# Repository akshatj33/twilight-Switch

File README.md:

# twilight-Switch
This is the embedded C code and the schematic and board layout for my project on twilight switch.

The timely operation of street lights, porch lights and other forms of outdoor illumination is required for the twin
concerns of safety and environment protection; lights operated too late are a safety hazard, while lights operated
too early are a waste of power. The switching on and off of external lightings can be set with the help of the device
called Twilight Switch.
Traditionally switching has been controlled via a human operator or the automatic control is accomplished
using a light sensor like LDR, photosensitive cells etc. However the use of sensors is accompanied by
wastage of power deterioration over time due to incessant exposure to atmosphere and environmental
changes leading to regular maintenance.
A Twilight switch provides a mechanism by which a light bulb can be turned ON and OFF automatically
without human interference. This project is a time based solution. This mechanism works on civil twilight
time. Component used for human interface is LCD where data such as date, month, year, city and the
present time (hh:mm:ss) are entered. From the algorithm, twilight time i.e. civil-dusk and civil-dawn time of
that place is calculated.
RTC (PCF8563) is used to maintain time. As an when the civil dusk time matches with RTC, the light (here
bulb) is switched ON and remains in this state till civil-dawn time where it is toggled.
We have fabricated 2 boards. First (4*3) is the DC Circuit board which has our microcontroller
(MSP430G2553) and LCD (HD44780U). Second (3*1) is the AC circuit board which has a triac (BT136)
whose 2 of the 3 gate requires AC. We are using triac instead of a relay because SSD switches are better
than mechanical ones. To isolate the AC portion of the circuit from the DC one we have used an optoisolator
(MOC 3041).

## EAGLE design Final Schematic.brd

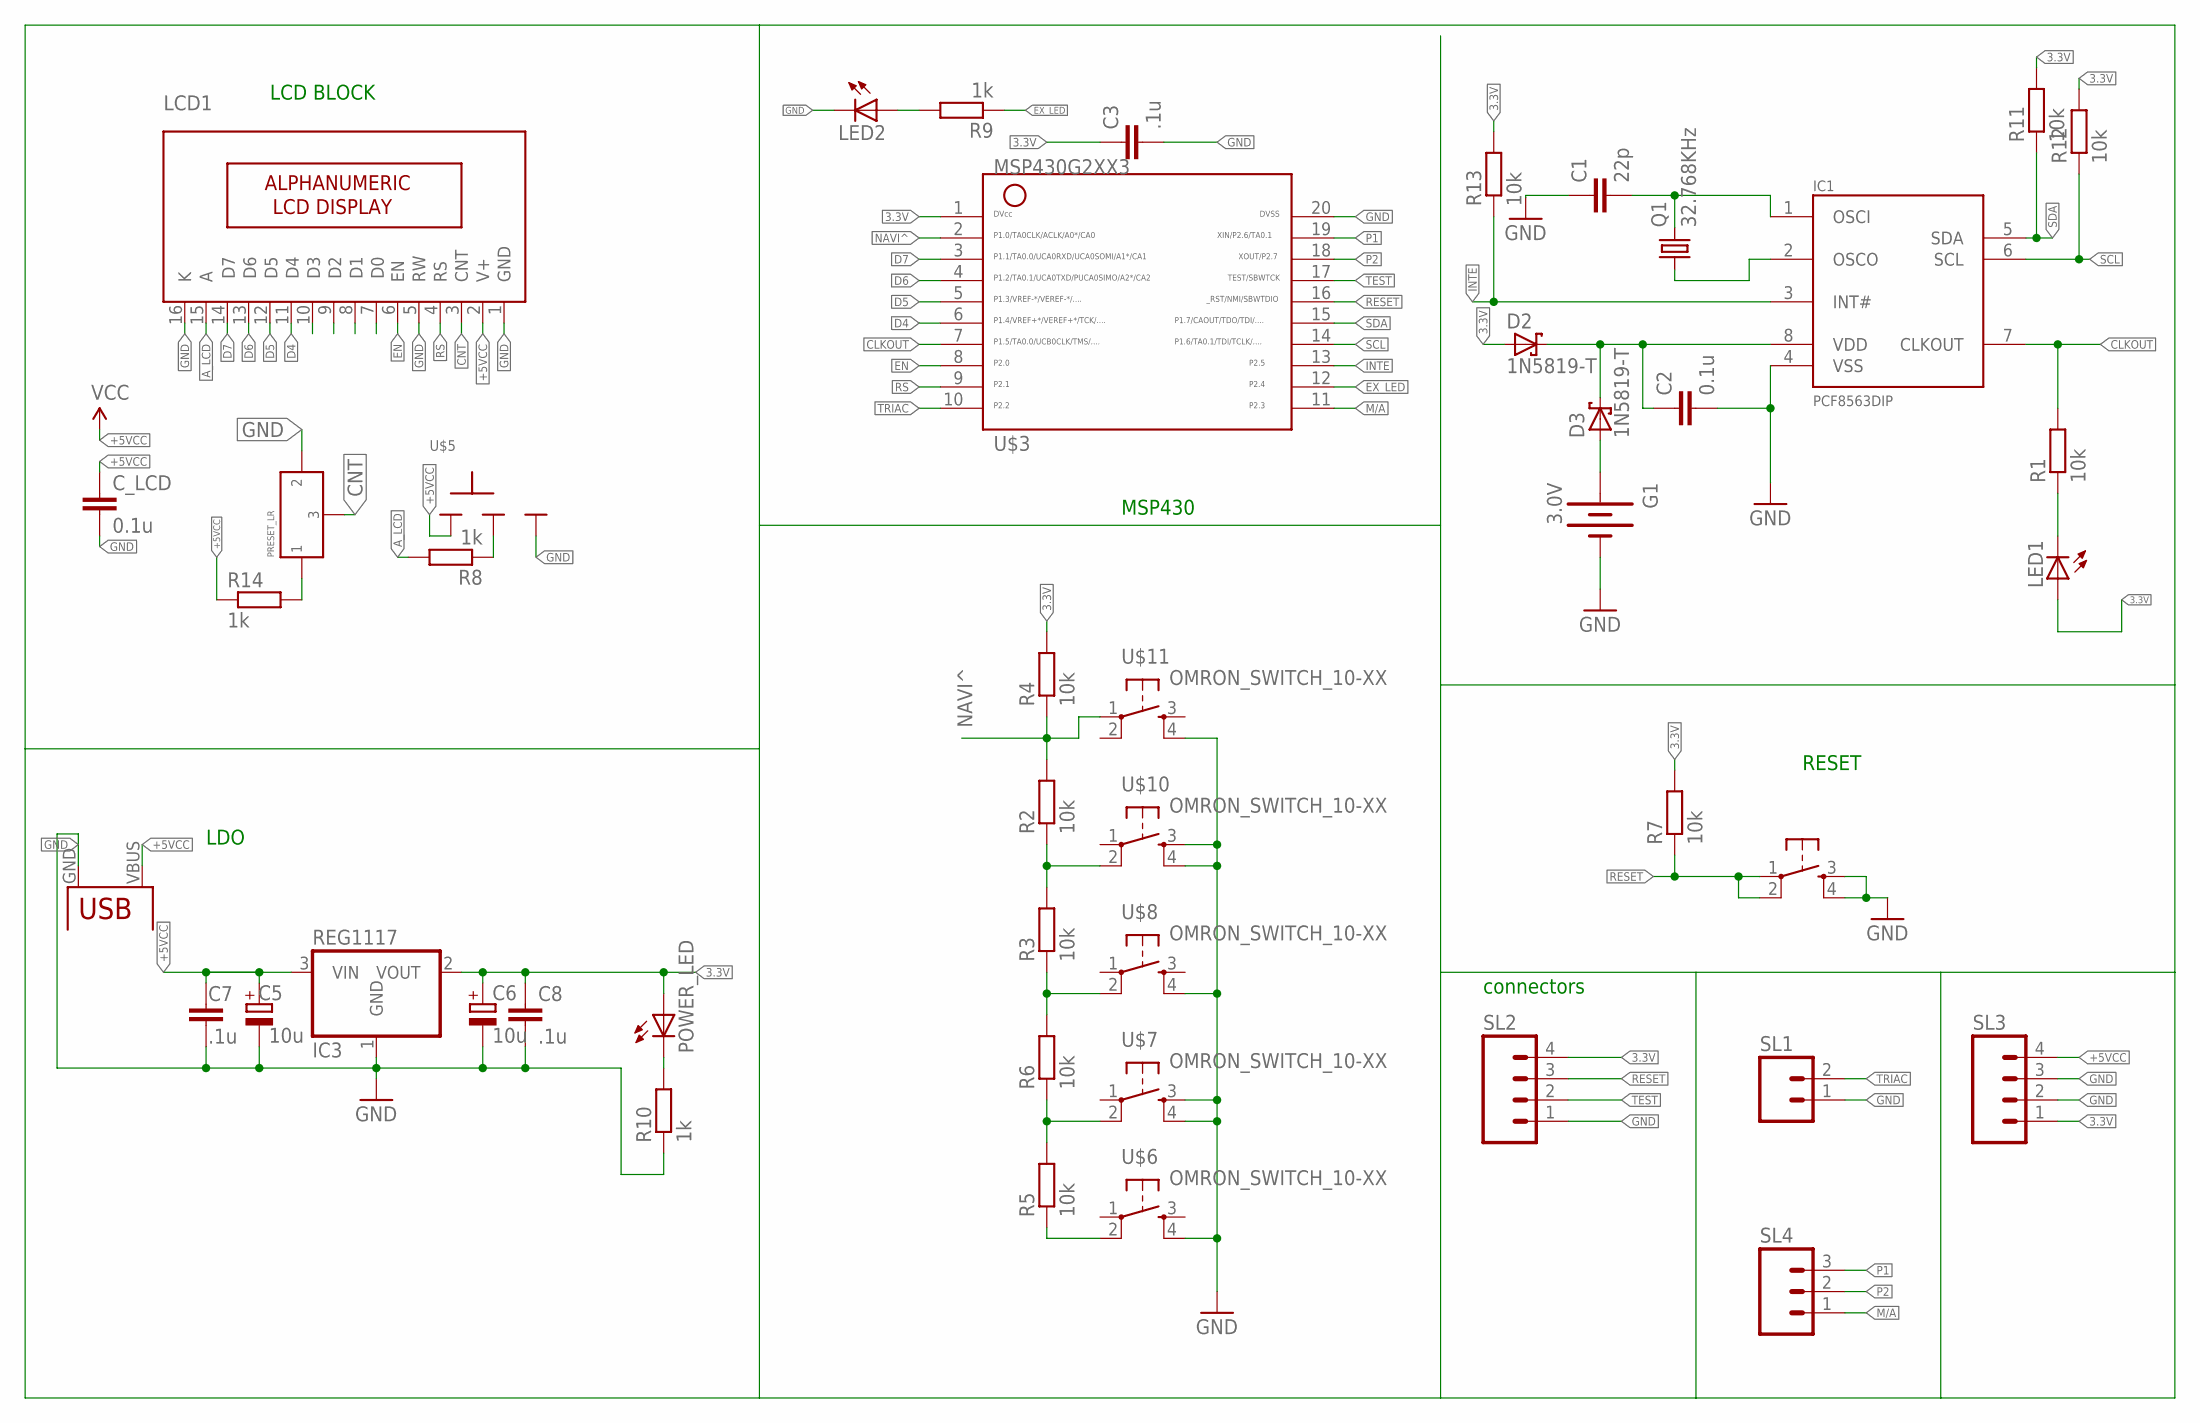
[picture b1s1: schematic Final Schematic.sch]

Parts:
C1: 22p; C025-025X050
C2: 0.1u; C025-025X050
C3, C7, C8: .1u; C025-025X050
C5, C6: 10u; E2,5-5
C_LCD: 0.1u; C025-025X050
D2, D3: 1N5819-T; DO41-7.6
G1: 3.0V; BATTCOM_20MM_PTH
IC1: PCF8563DIP; DIL08
IC3: REG1117; SOT223
LCD1: 16X2LCD; 16X2_LCD
LED1, LED2: LED3MM
POWER_LED: LED3MM
Q1: 32.768KHz; TC26H
R1, R2, R3, R4, R5, R6, R7, R11, R13: 10k; 0207/7
R8, R10, R14: 1k; 0207/7
R9: 1k; 0207/10
R12: 10k; 0207/10
SL1: M02; 02P
SL2, SL3: M04; 04P
SL4: M03; 03P
U$1: PRESET_LR
U$2: USB(POWER)
U$3: MSP430G2553DIP20; G2553-DIP20
U$5: SLIDESWITCH-BIG; BIGSWITCH
U$6, U$7, U$8, U$9, U$10, U$11: OMRON_SWITCH_10-XX; B3F-10XX

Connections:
3.3V: C3.1, C6.+, C8.1, D2.A, IC3.2 (VOUT), LED1.A, POWER_LED.A, R4.2, R7.2, R11.2, R12.2, R13.2, SL2.4, SL3.1, U$3.1
+5VCC: C5.+, C7.1, C_LCD.1, IC3.3 (VIN), LCD1.2 (V+), R14.1, SL3.4, U$2.VBUS (VCC), U$5.1
A_LCD: LCD1.15 (A), R8.2
CLKOUT: IC1.7 (CLKOUT), R1.2, U$3.7
CNT: LCD1.3 (CNT), U$1.P$3 (3)
D4: LCD1.11 (D4), U$3.6
D5: LCD1.12 (D5), U$3.5
D6: LCD1.13 (D6), U$3.4
D7: LCD1.14 (D7), U$3.3
EN: LCD1.6 (EN), U$3.8
EX_LED: R9.1, U$3.12
GND: C1.1, C2.2, C3.2, C5.-, C6.-, C7.2, C8.2, C_LCD.2, G1.2 (-), IC1.4 (VSS), IC3.1 (GND), LCD1.1 (GND), LCD1.5 (RW), LCD1.16 (K), LED2.K (C), R10.1, SL1.1, SL2.1, SL3.2, SL3.3, U$1.P$2 (2), U$2.GND, U$3.20, U$5.3, U$6.4 (S1), U$7.3 (S), U$7.4 (S1), U$8.4 (S1), U$9.3 (S), U$9.4 (S1), U$10.3 (S), U$10.4 (S1), U$11.4 (S1)
INTE: IC1.3 (INT#), R13.1, U$3.13
M/A: SL4.1, U$3.11
unnamed: R8.1, U$5.2
unnamed: LED2.A, R9.2
unnamed: LED1.K (C), R1.1
unnamed: R14.2, U$1.P$1 (1)
unnamed: R5.1, U$6.2 (P1)
unnamed: R2.1, R3.2, U$10.2 (P1)
unnamed: POWER_LED.K (C), R10.2
unnamed: R3.1, R6.2, U$8.2 (P1)
unnamed: C2.1, D2.C, D3.C, IC1.8 (VDD)
unnamed: C1.2, IC1.1 (OSCI), Q1.2
unnamed: IC1.2 (OSCO), Q1.1
unnamed: D3.A, G1.1 (+)
unnamed: R5.2, R6.1, U$7.2 (P1)
NAVI^: R2.2, R4.1, U$3.2, U$11.1
P1: SL4.3, U$3.19
P2: SL4.2, U$3.18
RESET: R7.1, SL2.3, U$3.16, U$9.1, U$9.2 (P1)
RS: LCD1.4 (RS), U$3.9
SCL: IC1.6 (SCL), R12.1, U$3.14
SDA: IC1.5 (SDA), R11.1, U$3.15
TEST: SL2.2, U$3.17
TRIAC: SL1.2, U$3.10

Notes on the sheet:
LCD BLOCK
RESET
connectors
LDO
MSP430

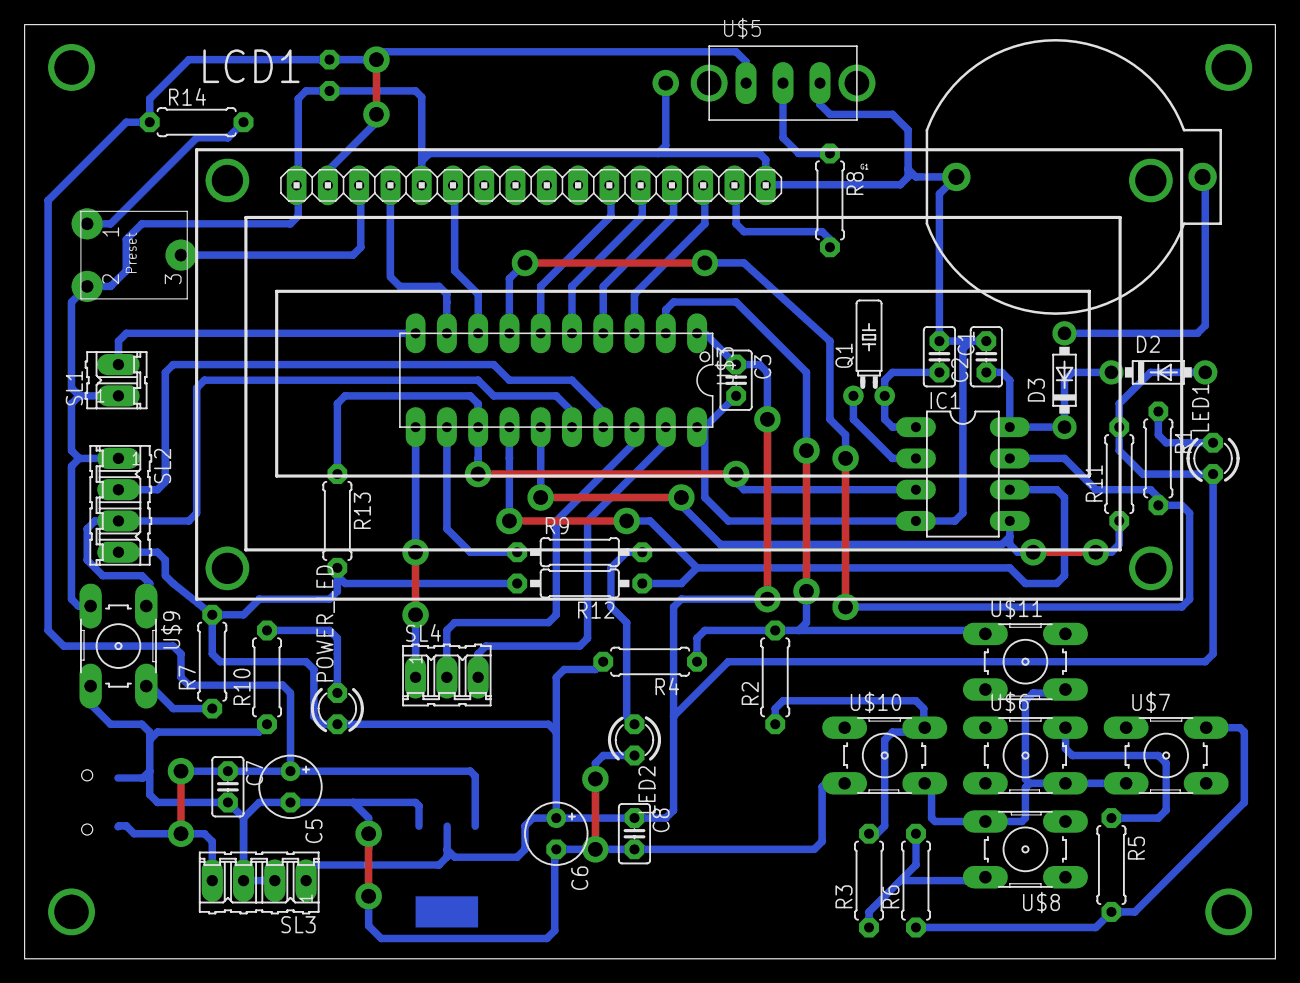
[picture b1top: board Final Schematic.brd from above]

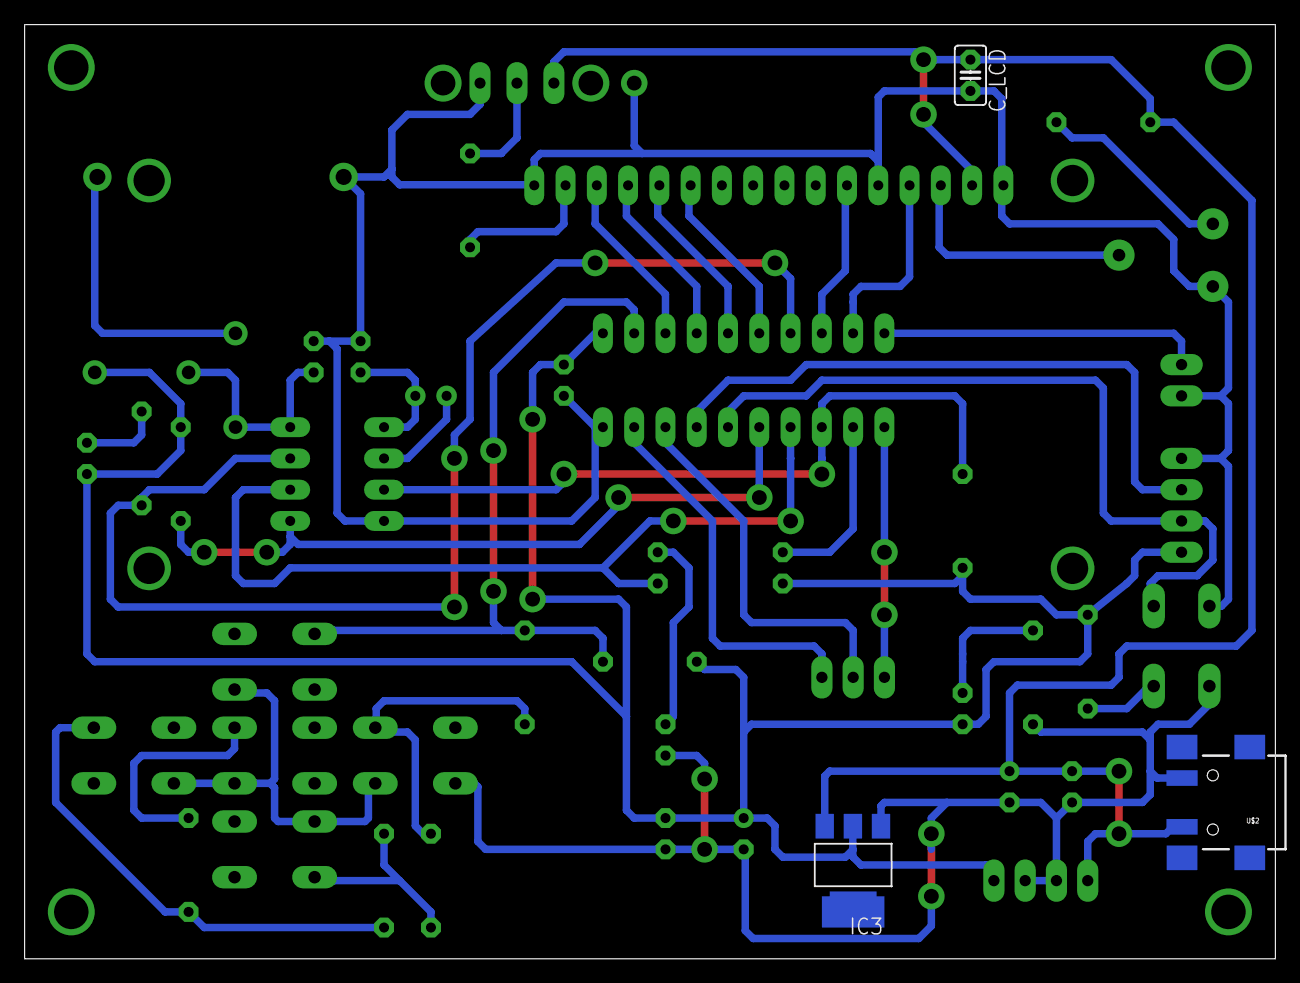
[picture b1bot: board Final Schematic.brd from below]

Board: 2 copper layers, 101.6 x 75.9 mm, 46 parts (3 on the bottom side), 36 nets.

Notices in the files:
parts and their libraries:
SparkFun-Electromechanical: Licensing: Creative Commons ShareAlike 4.0 International - https://creativecommons.org/licenses/by-sa/4.0
